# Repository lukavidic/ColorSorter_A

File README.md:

# 🎨 Color Sorter

## Projekat iz predmeta Mikrokontrolerski sistemi

**ColorSorter** je pametni sistem za automatsko razvrstavanje pločica po bojama. Projekat je razvijen u okviru predmeta *Mikrokontrolerski sistemi* i koristi:
- senzor boja
- servo motor za upravljanje mehanizmom sortiranja
- Wi-Fi modul za bežičnu komunikaciju

## Cilj projekta

Cilj je omogućiti **brzo, precizno i pametno sortiranje pločica** uz real-time komunikaciju i nadzor. Sistem je osmišljen tako da može raditi autonomno, kao i pod nadzorom korisnika putem aplikacije. Sve zahtjeve možete pogledati na **Wiki** stranici - [O projektu](https://github.com/lukavidic/ColorSorter_A/wiki/2.-O-projektu) kao i [dostupne i potrebne komponente](https://github.com/lukavidic/ColorSorter_A/wiki/3.-Dostupne-i-potrebne-komponente).

---

## Realizacija projekta

Razvoj sistema je tekao kroz sledeće faze:

1.  **Kreiranje električne šeme**
   
    Na samom početku kreirana je električna šema, koja prikazuje sve povezane komponente i njihovu funkcionalnu ulogu u realizaciji ovog projekta.
    Detalje možete pronaći na **Wiki** stranici – [Projektovanje električne šeme u alatu KiCAD](https://github.com/lukavidic/ColorSorter_A/wiki/4.-Projektovanje-elektri%C4%8Dne-%C5%A1eme-u-alatu-KiCAD).

2.  **Izrada PCB-a**
   
    Na osnovu električne šeme, dizajnirana je štampana ploča (PCB) koja omogućava stabilno napajanje i povezivanje svih perifernih komponenti.
    PCB sadrži:

      - Mikrokontroler PIC24FJ64GA702 kao centralnu upravljačku jedinicu

      - Pasivne komponente (otpornici, kondenzatori)
  
      - Regulatore napona
  
      - Konektore i pinove za povezivanje sa eksternim uređajima kao što su senzor boja, servo motor te WiFi modul
    
    Više o dizajnu ploče dostupno je na **Wiki** stranici – [Projektovanje PCB-a u alatu KiCAD](https://github.com/lukavidic/ColorSorter_A/wiki/4.-Projektovanje-elektri%C4%8Dne-%C5%A1eme-u-alatu-KiCAD).

3.  **Programiranje mikrokontrolera**
   
    Nakon hardverske realizacije, implementiran je kod za rad uređaja – uključujući očitavanje boja, kontrolu motora i Wi-Fi komunikaciju, čiju dokumentaciju kompletnog koda možete pronaći na **Wiki** stranici - [Programiranje mikrokontrolera](https://github.com/lukavidic/ColorSorter_A/wiki/6.-Programiranje-mikrokontrolera).

4. **Izrada aplikacije**

   Nakon uspješnog programiranja mikrokontrolerske pločice, pristupili smo razvoju desktop aplikacije koja omogućava nadzor i upravljanje procesom razvrstavanja boja. Aplikacija komunicira sa uređajem putem WiFi veze i omogućava korisniku da prati status sistema u realnom vremenu, šalje komande za pokretanje i resetovanje, te definiše pravila sortiranja po bojama. O zahtjevima aplikacije možete pogledati na **Wiki** stranici - [Firmware i aplikacija](https://github.com/lukavidic/ColorSorter_A/wiki/7.-Firmware-i-aplikacija).

5.  **Testiranje i kalibracija**
   
    Sistem je prolazio kroz više faza testiranja kako bi se obezbijedila tačnost u detekciji boja i pravilno sortiranje. Kratak pogled u testiranje komponenata možete pronaći na **Wiki** stranici - [Testiranje rada komponenata](https://github.com/lukavidic/ColorSorter_A/wiki/7.-Testiranje-rada-komponenata).

---

## Autori
- Ana Vulin  
- Anđela Savičić  
- Luka Zeljko

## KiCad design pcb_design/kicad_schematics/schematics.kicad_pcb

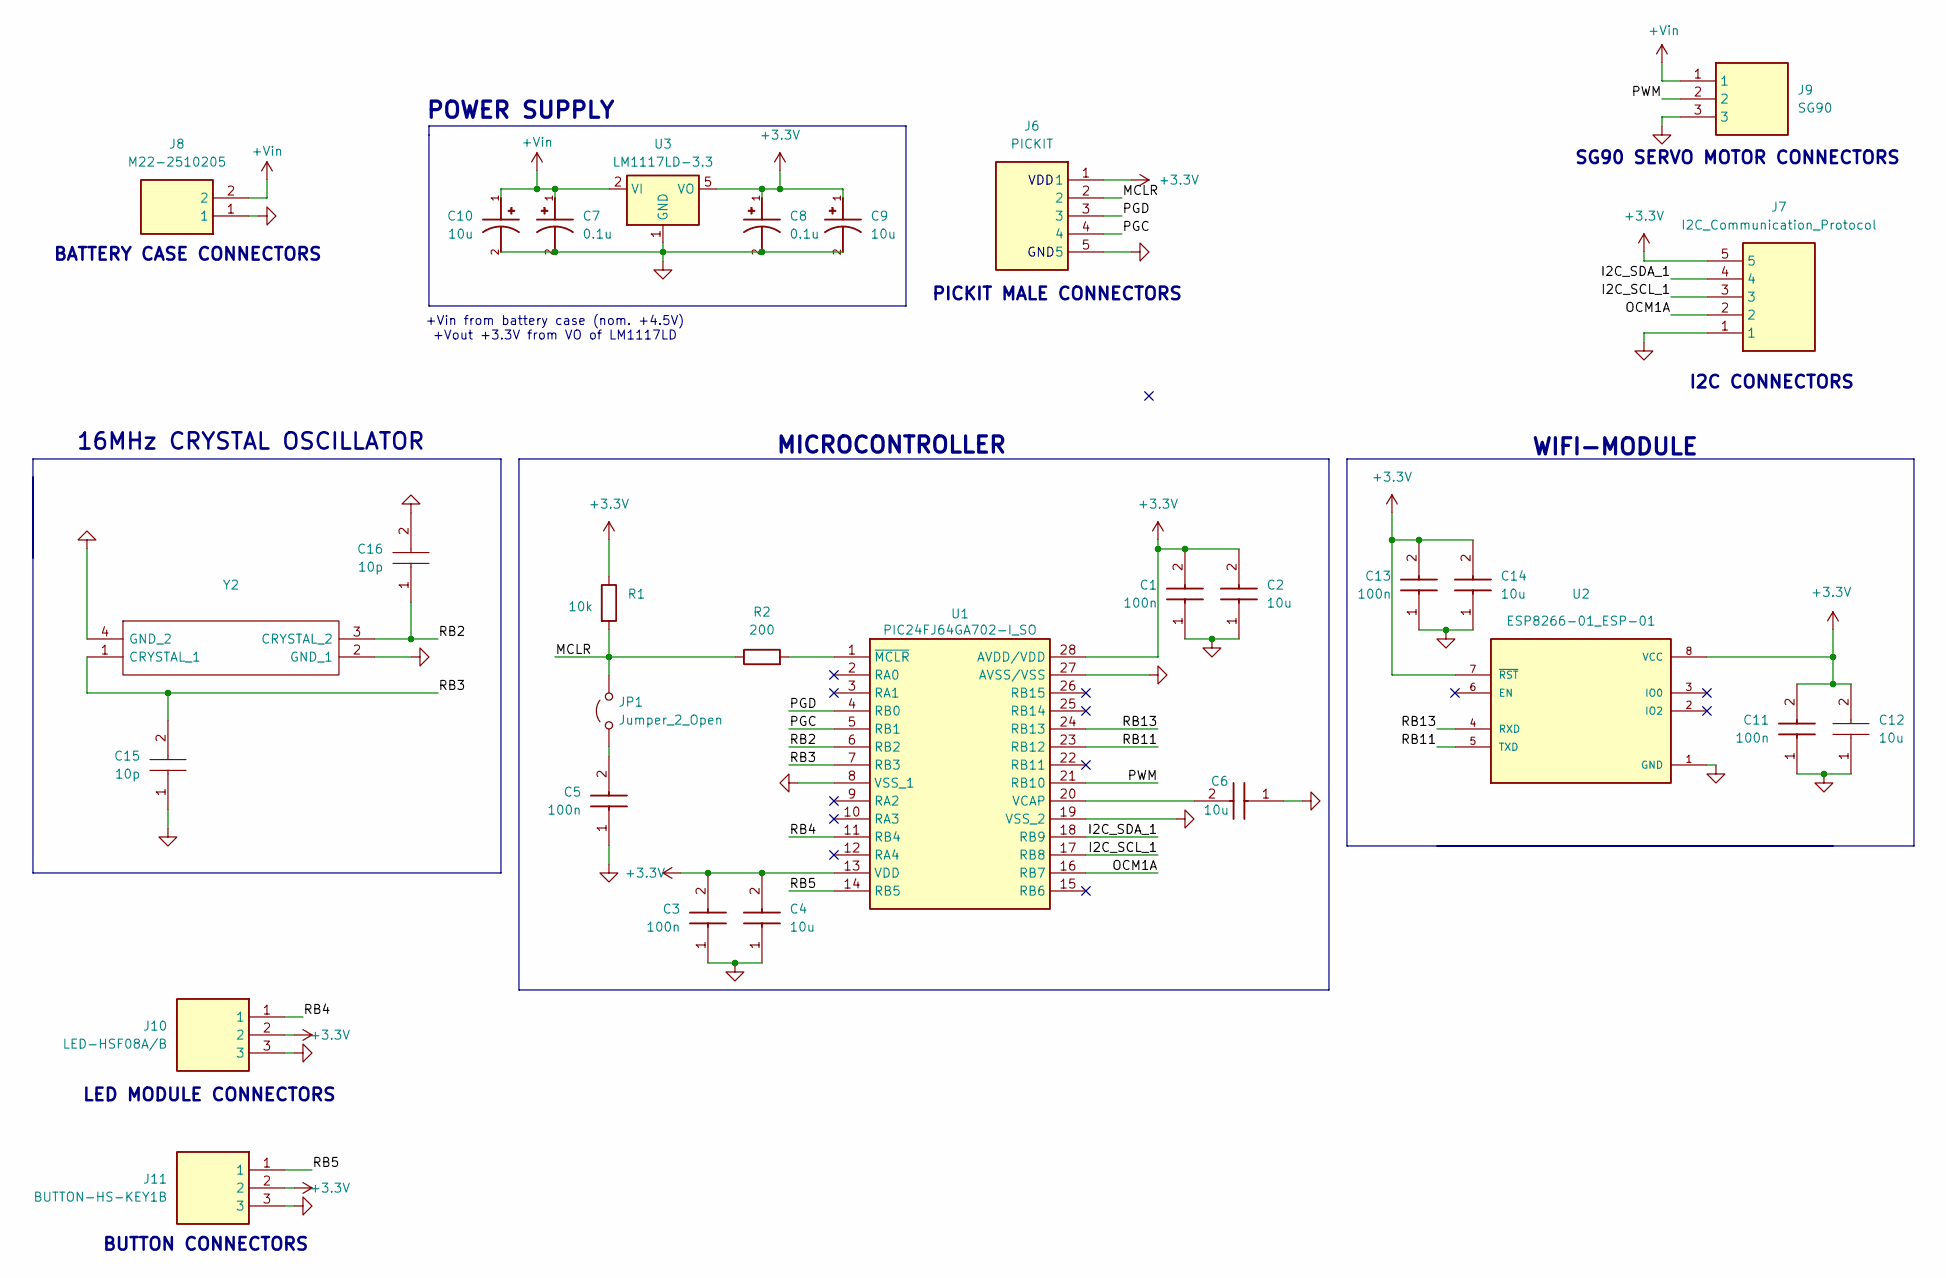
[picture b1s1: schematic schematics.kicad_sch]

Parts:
C1, C3, C5, C11, C13: 100n; C0402; Mouser Part Number 80-C0402C104M4P
C2, C4, C6, C12, C14: 10u; C0805; Mouser Part Number 80-C0805C106M4P
C7, C8: 0.1u; CAPAE430X550N
C9, C10: 10u; CAPPRD200W50D500H1250
C15, C16: 10p; CAPC0603X33N; Mouser Part Number 581-02013A100J
J6: PICKIT; HDRV5W64P0X254_1X5_1270X254X610P; Mouser Part Number 855-M20-9990546
J7: I2C_Communication_Protocol; HDRV5W64P0X254_1X5_1270X254X610P; Mouser Part Number 855-M20-9990546
J8: M22-2510205; HDRV2W60P0X200_1X2_400X200X525P; Mouser Part Number 855-M22-2510205
J9: SG90; HDRV3W60P0X200_1X3_600X200X525P; Mouser Part Number 855-M22-2510305
J10: LED-HSF08A/B; HDRV3W60P0X200_1X3_600X200X525P; Mouser Part Number 855-M22-2510305
J11: BUTTON-HS-KEY1B; HDRV3W60P0X200_1X3_600X200X525P; Mouser Part Number 855-M22-2510305
JP1: Jumper_2_Open; HDRV2W60P0X200_1X2_400X200X525P
R1: 10k; ERA8KEB1004V
R2: 200; RESC3216X70N
U1: PIC24FJ64GA702-I_SO; SOIC127P1030X265-28N; Mouser Part Number 579-24FJ64GA702ISO
U2: ESP8266-01_ESP-01; XCVR_ESP8266-01_ESP-01; PARTREV V1.2
U3: LM1117LD-3.3; WSON-8-1EP_4x4mm_P0.8mm_EP2.2x3mm
Y2: 16MHz crystal; 830108288709; Mouser Part Number 710-830108288709

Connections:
+3.3V: C1.2, C2.2, C3.2, C4.2, C8.1, C9.1, C11.2, C12.2, C13.2, C14.2, J6.1, J7.5, J10.2, J11.2, R1.1, U1.13 (VDD), U1.28 (AVDD/VDD), U2.7 (~RST), U2.8 (VCC), U3.5 (VO), U3.6 (VO), U3.7 (VO), U3.9 (VO); also elsewhere on the board
+Vin: C7.1, C10.1, J8.2, J9.1, U3.2 (VI), U3.3 (VI), U3.4 (VI)
/I2C_SCL_1: J7.3, U1.17 (RB8)
/I2C_SDA_1: J7.4, U1.18 (RB9)
/MCLR: J6.2, JP1.2 (B), R1.2, R2.1
/OCM1A: J7.2, U1.16 (RB7)
/PGC: J6.4, U1.5 (RB1)
/PGD: J6.3, U1.4 (RB0)
/PWM: J9.2, U1.21 (RB10)
/RB2: C16.1, U1.6 (RB2), Y2.3 (CRYSTAL_2)
/RB3: C15.2, U1.7 (RB3), Y2.1 (CRYSTAL_1)
/RB4: J10.1, U1.11 (RB4); also elsewhere on the board
/RB5: J11.1, U1.14 (RB5)
/RB11: U1.23 (RB12), U2.5 (TXD)
/RB13: U1.24 (RB13), U2.4 (RXD)
GND: C1.1, C2.1, C3.1, C4.1, C5.1, C6.1, C7.2, C8.2, C9.2, C10.2, C11.1, C12.1, C13.1, C14.1, C15.1, C16.2, J6.5, J7.1, J8.1, J9.3, J10.3, J11.3, U1.8 (VSS_1), U1.19 (VSS_2), U1.27 (AVSS/VSS), U2.1 (GND), U3.1 (GND), Y2.2 (GND_1), Y2.4 (GND_2); also elsewhere on the board
unnamed: C5.2, JP1.1 (A)
unnamed: C6.2, U1.20 (VCAP)
unnamed: R2.2, U1.1 (~MCLR)

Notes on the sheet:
MICROCONTROLLER
PICKIT MALE CONNECTORS
LED MODULE CONNECTORS
SG90 SERVO MOTOR CONNECTORS
GND
POWER SUPPLY
BUTTON CONNECTORS
BATTERY CASE CONNECTORS
+Vin from battery case (nom. +4.5V) +Vout +3.3V from VO of LM1117LD
I2C CONNECTORS
16MHz CRYSTAL OSCILLATOR
WIFI-MODULE
VDD

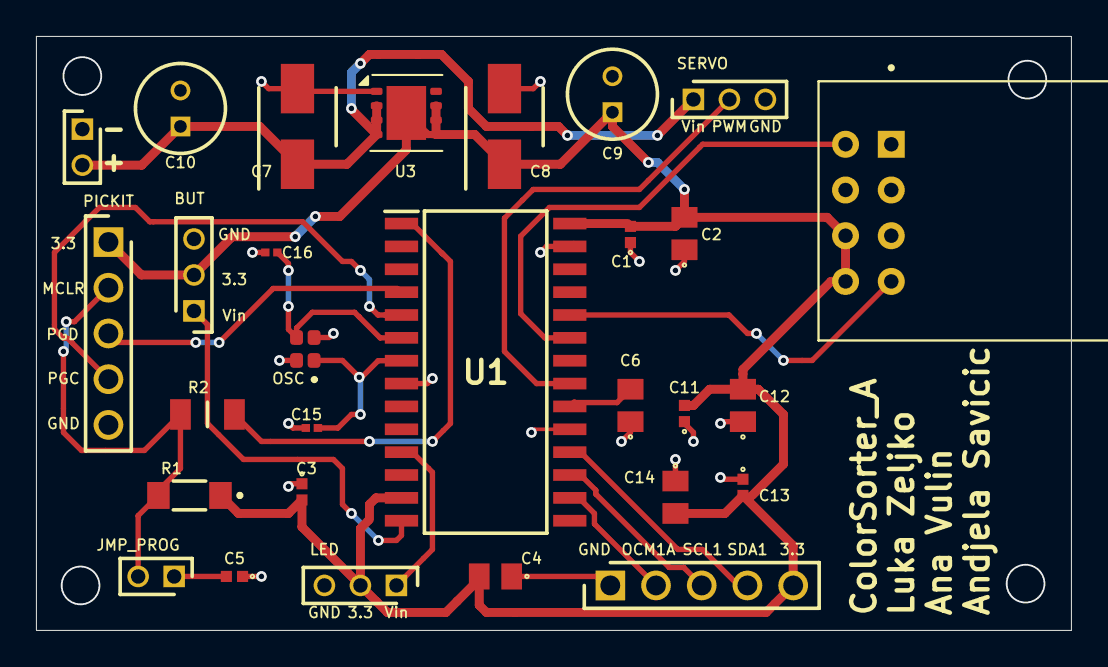
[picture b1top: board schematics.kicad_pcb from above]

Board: 2 copper layers, 57.5 x 33.0 mm, 29 parts (0 on the bottom side), 19 nets.

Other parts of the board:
LED: LED-HSF08A/B; HDRV3W60P0X200_1X3_600X200X525P

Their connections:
+3.3V: LED.2; also elsewhere on the board
/RB4: LED.1; also elsewhere on the board
GND: LED.3; also elsewhere on the board

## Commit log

2024-11-29 Minimalna konfiguracija mikorkontrolera u kicadu
2024-12-02 Dodani odgovarajuci kondezatori u schematics.
2024-12-03 Dodane vrijednosti ostalih otpornika i kondenzatora u minimalnoj konf
2024-12-03 Wi-Fi modul dodan u KiCAD
2024-12-09 #16 Dokumentovani modul Color 10 Click(RGB senzor) dodati u KiCad semu Izvuceni su pinovi I2C i pin za DI komunikacije
2024-12-09 Obrisan #auto_saved_files#
2024-12-10 sema
2024-12-11 obrisani nepotrebni fajlovi
2024-12-11 Dodatak za gitignore
2024-12-11 Brisanje nepotrebnog fajla
2024-12-11 ICSP pinovi
2024-12-11 Dodani modeli koristeni u KiCAD-u
2024-12-11 #11 Analiza power supply šeme Dodan je lin. regulator u semi
2024-12-11 Dodajem modele X5R capacitors koji su korišćeni u šemi
2024-12-13 Komentari sastanka
2024-12-18 Dodani decoupling kondenzatori kod wifi modula i regulatora
2024-12-18 Dodan eksterni oscilator
2024-12-28 Dodani pin headers i odgovarajući modeli koji se koriste u šemi
2024-12-29 Uredjena šema sa dodanim pin konektorima.
2024-12-29 Obrisan fajl.
2025-01-13 13.1.25, dodani footprinti i inicijalna sema pcba
2025-01-15 Prva verzija pcb.
2025-01-23 Inicijalno rutiranje, dodani i neki 3d modeli
2025-01-25 Dodani modeli ostalih komponenata u models, Podebljane zice koje nose napajanje, wifi modul okrenut, dodane oznake elemenata
2025-01-25 Obrisan nepotreban fajl
2025-01-29 Ispravljene greske sa sastanka
2025-01-29 Ispravljen warning
2025-01-30 Promijenjeni simboli nekih komponenti
2025-01-30 promjena C5.
2025-01-30 Povecan font imena inzenjera
2025-01-30 Dodajem gotovu listu komponenata.
2025-01-30 Dodane rupe u coskove pcb-a za sarafljenje
2025-01-30 Dodan mikrokontroler komponenta u listu materijala.
2025-03-18 Initial project structure
2025-03-18 Dodane init linije u .h i .c fajlove
2025-03-18 Dodani gerber fajlovi
2025-03-18 Prepravljanje nekih inkludova kod .h fajlova i dodan inc.h
2025-03-18 Struktura koda prilagodjena MPLAB-u
2025-03-18 Bugfix oko mplaba
2025-03-18 Dodana init funkcija za color 10 click senzor
2025-03-18 Popravljan i2c
2025-03-19 Testiranje I2C
2025-03-19 Added init function for wifi module
2025-03-24 Added comments on wifi module functions
2025-03-27 Changed Clock frequency to 32MHz => FCY=16MHz
2025-03-31 Initial application structure and code
2025-04-01 Dodano pomjeranje boja u desktop aplikaciji
2025-04-02 Integrisan color detection upotrebom WS2812 I VEML3328
2025-04-02 Dodani u inc.h potrebni define
2025-04-02 Prilagodjen servo motor novoj frekvenciji
2025-04-02 Wifi modul funkcije prije pull-a
2025-04-02 Rebase
2025-04-03 Danas uradjeno P.S. integracija ws2812 i veml3328
2025-04-04 Nova ocitavanja za boje
2025-04-04 Dodana prekidana rutina za reset pritiskom dugmeta.
2025-04-05 Testovi komunikacije, nedovrseno
2025-04-05 Integrisani color click i servo motor, rade skupa
2025-04-05 Promijenjene boje u testu u mainu
2025-04-07 Danasnje promjene.
2025-04-09 Dodata nova ocitavanja za boje.
2025-04-11 Natjeran wifi modul da odgovori sa OK na AT
2025-04-12 Natjeran wifi modul da se poveze na etfbl.net i vrati ip adresu koju mu je mreza dodijelila
2025-04-12 Na pritisak misom na all left dugme u user app natjeran servo motor da se pomjeri u desno
2025-04-12 Na pritisak lijevog dugmeta u app, servo lijevo, na pritisak desnog, servo desno
2025-04-12 Priprema wifi_dev grane za merge sa main
2025-04-12 Removed conflict marker
2025-04-12 Obrisane linije vezane za wifi modul koje se ne koriste vise
2025-04-14 Uklonjeno koristenje uart1 kanala od strane color sensora, start stop omoguceni iz korisnicke aplikacije
2025-04-14 Testirana nova ocitavanja sa obrnutim zetonima i popravljena funkcija color distance.
2025-04-15 Sve boje lijevo i sve boje desno dugmad rade, start stop iz app radi, ali kad se restartuje pomocu pickita
2025-04-26 Example of documentation
2025-05-05 Added documentation for wifi module
2025-05-05 Dopunjena dokumentacija za wifi i dokumentovan inc.h
2025-05-05 Added desktop app documentation
2025-05-07 Dokumentacija coloe sensora i i2c funckija koje se koriste
2025-05-07 Dokumentacija za button.
2025-05-07 Dodane dokumentacije main.c fajla, servoa i ostale dopunjene
2025-05-07 Dodana doxygen dokumentacija firmware-a u /docs/firmware_docs i software dokumentacija u /docs/software_docs
2025-05-11 izmijena u button-u.
2025-05-12 Dodajem fajl *.txt sa link-om promo videa.
